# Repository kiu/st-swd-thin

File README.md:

# st-swd-thin

A simple adapter for ST-LINK/V2 SWD to 6P

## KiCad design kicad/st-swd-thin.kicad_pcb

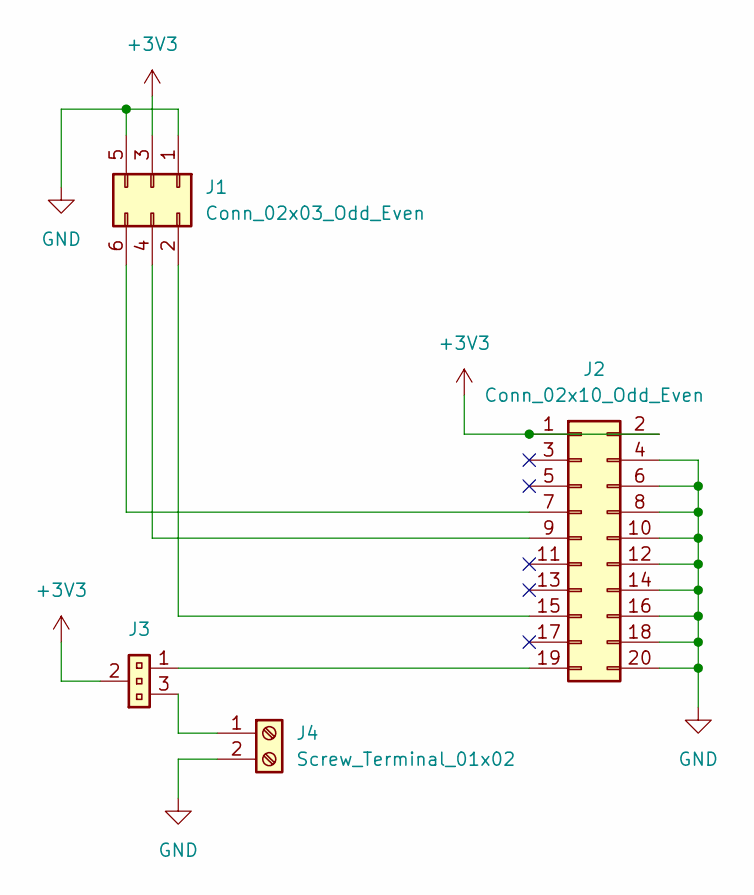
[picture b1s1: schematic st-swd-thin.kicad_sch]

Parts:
J1: Conn_02x03_Odd_Even; PinHeader_2x03_P2.54mm_Horizontal
J2: Conn_02x10_Odd_Even; IDC-Header_2x10_P2.54mm_Vertical
J3: 1x03_Jumper; PinHeader_1x03_P2.54mm_Vertical
J4: Screw_Terminal_01x02; TerminalBlock_bornier-2_P5.08mm

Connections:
+3V3: J1.3, J2.1, J2.2, J3.2
GND: J1.1, J1.5, J2.4, J2.6, J2.8, J2.10, J2.12, J2.14, J2.16, J2.18, J2.20, J4.2
unnamed: J1.2, J2.15
unnamed: J1.4, J2.9
unnamed: J1.6, J2.7
unnamed: J2.19, J3.1
unnamed: J3.3, J4.1

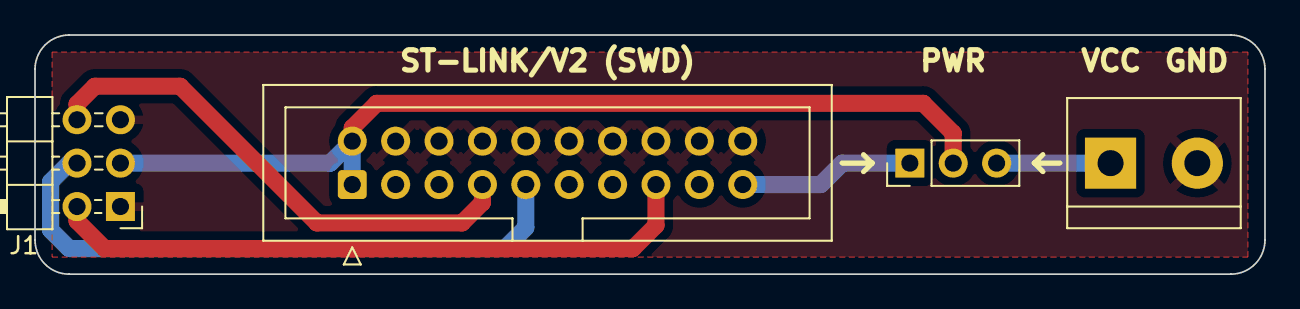
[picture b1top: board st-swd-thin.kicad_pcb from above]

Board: 2 copper layers, 72.0 x 14.0 mm, 4 parts (0 on the bottom side), 7 nets.
